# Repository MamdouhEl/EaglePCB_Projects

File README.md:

# EaglePCB_Projects
Here Eagle PCB projects can be found

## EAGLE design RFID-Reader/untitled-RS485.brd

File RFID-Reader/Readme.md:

This PCB was used to mount the "RI-STU-MRD2" RFID Reader Module and connect with Arduino Board and Kinco PLC.

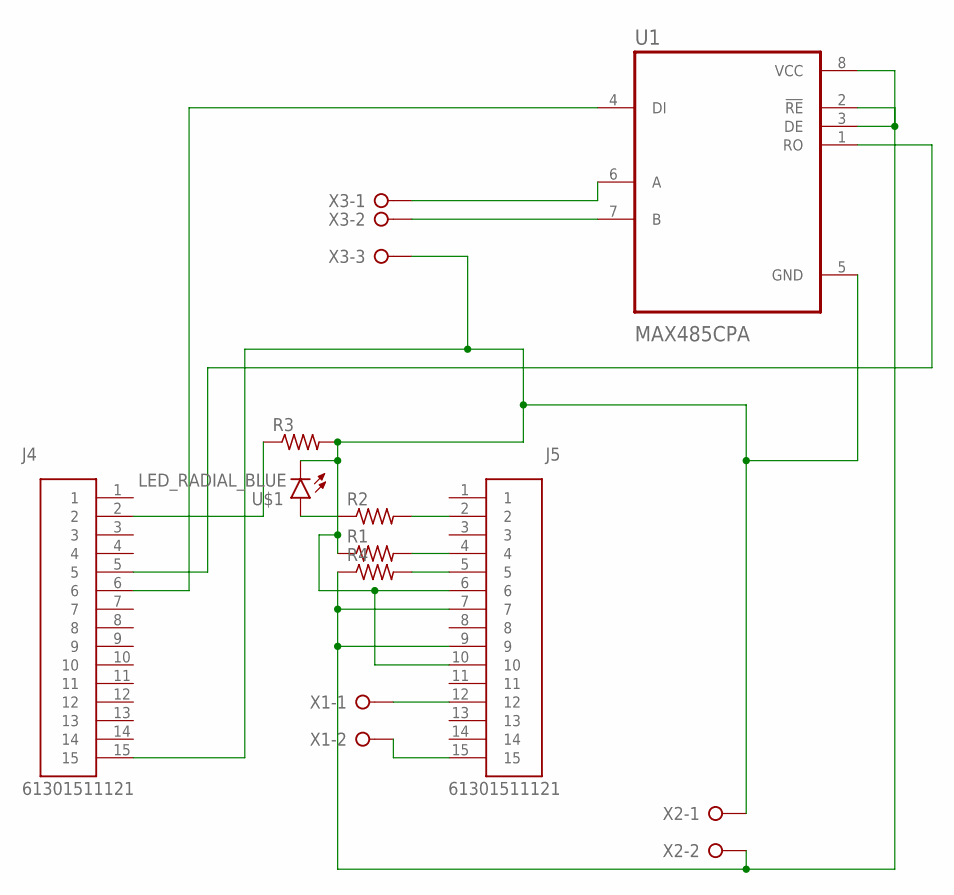
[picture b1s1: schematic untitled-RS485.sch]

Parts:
J4, J5: 61301511121
R1, R2, R3, R4: R-US_0207/7; 0207/7
U1: MAX485CPA; DIP794W47P254L991H457Q8
U$1: LED_RADIAL_BLUE; LEDRD254W60D565H860B_B
X1, X2: W237-02P; W237-132
X3: W237-03P; W237-133

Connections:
unnamed: J4.2, R3.1
unnamed: J5.5, R4.2
unnamed: J4.5, U1.1 (RO)
unnamed: J4.6, U1.4 (DI)
unnamed: J5.2, R2.2
unnamed: R2.1, U$1.1 (A)
unnamed: U1.7 (B), X3.2
unnamed: J5.4, R1.2
unnamed: J4.15, J5.6, J5.10, R1.1, R3.2, U1.5 (GND), U$1.2 (C), X2.1, X3.3
unnamed: U1.6 (A), X3.1
unnamed: J5.7, J5.9, R4.1, U1.2 (!RE), U1.3 (DE), U1.8 (VCC), X2.2
unnamed: J5.12, X1.1
unnamed: J5.15, X1.2

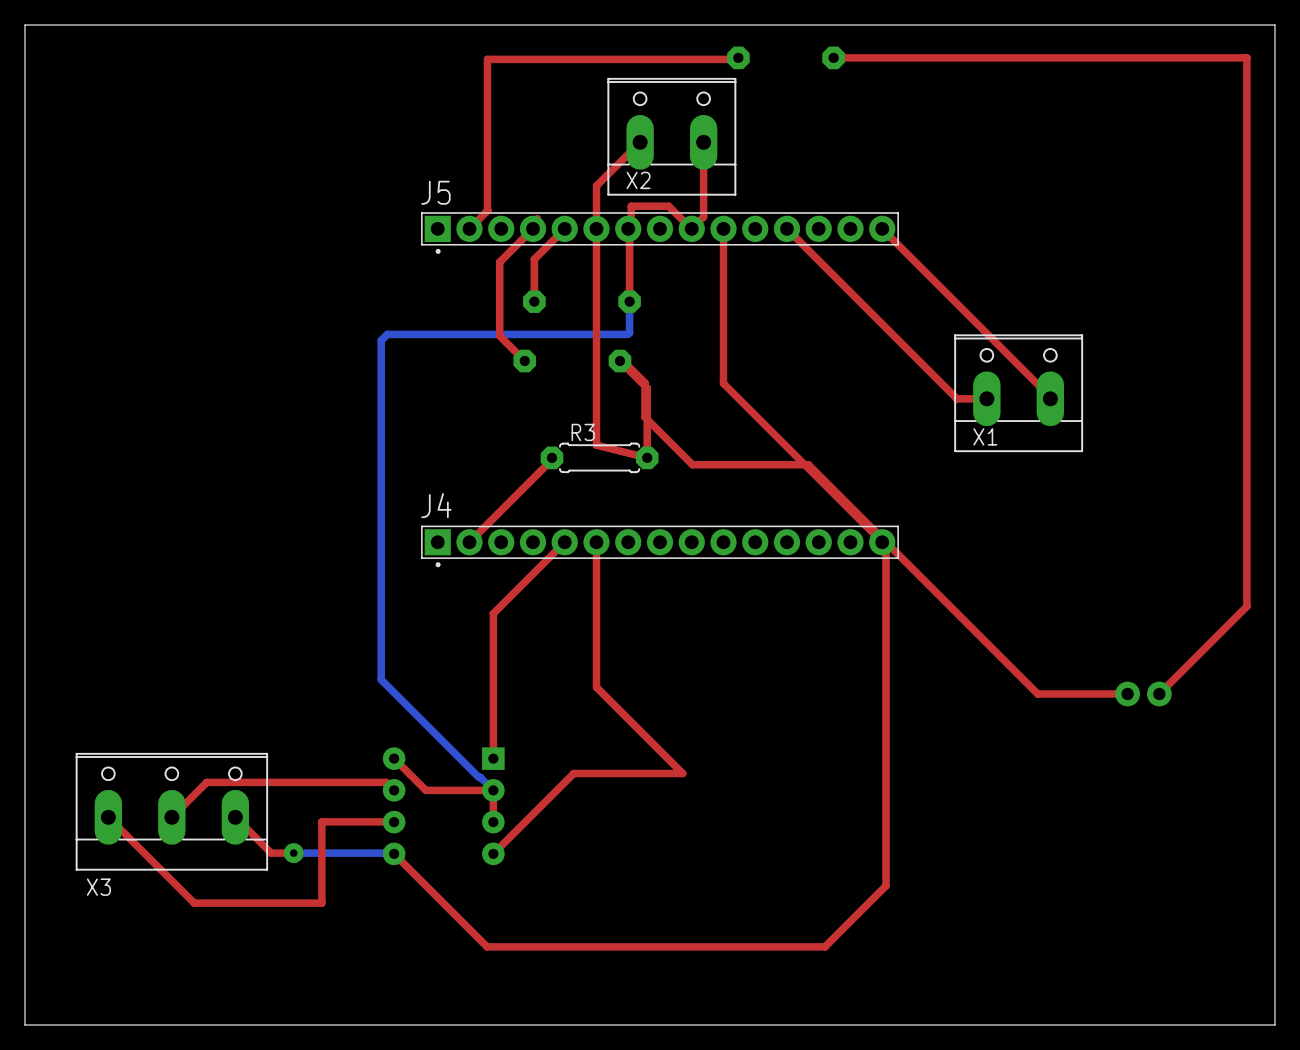
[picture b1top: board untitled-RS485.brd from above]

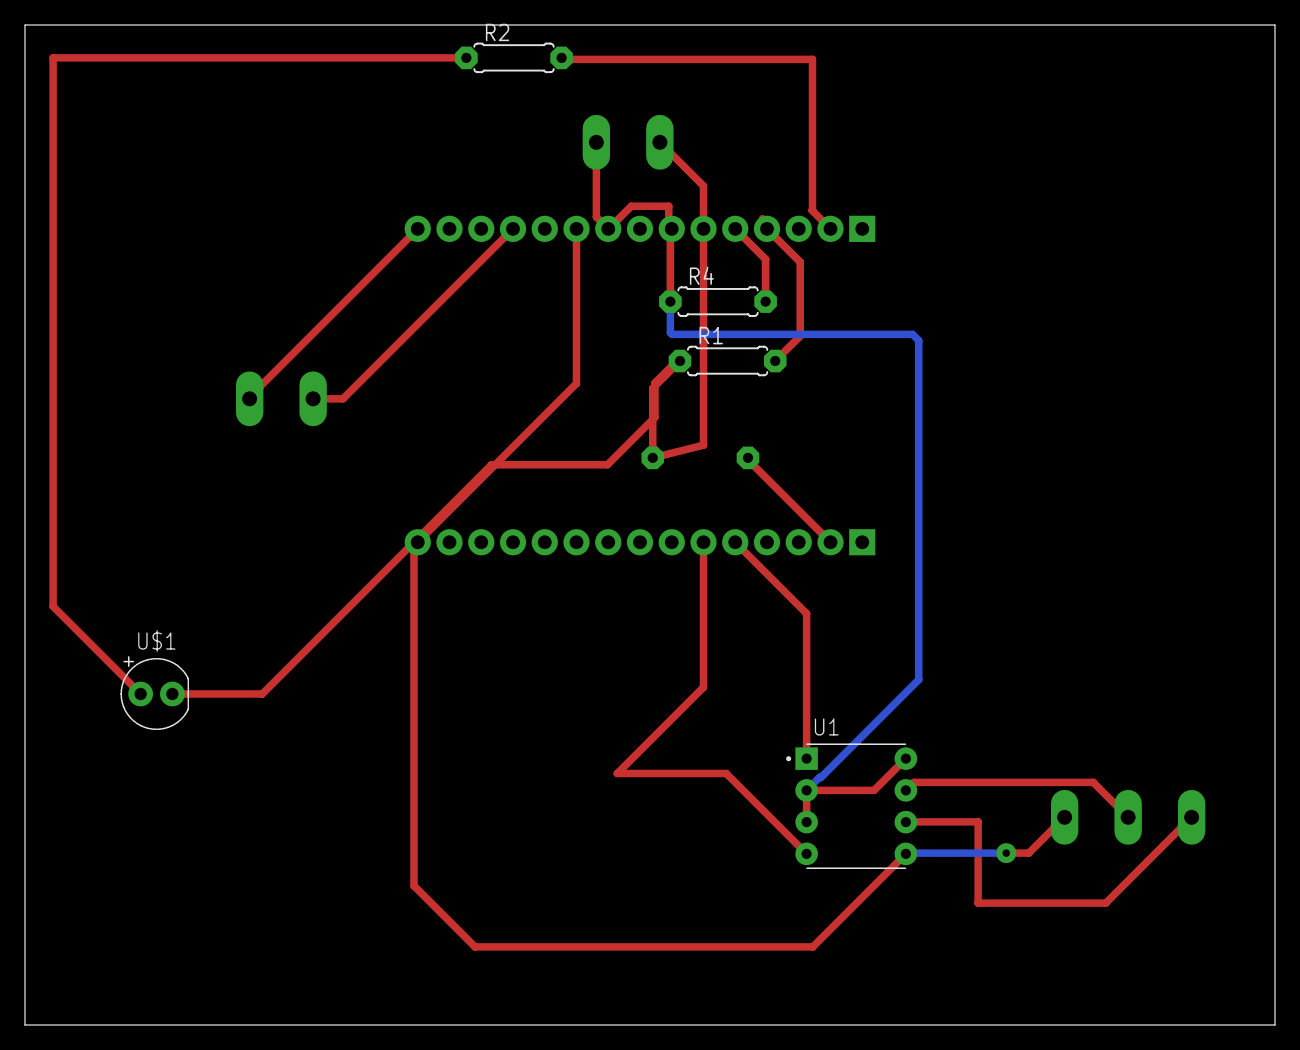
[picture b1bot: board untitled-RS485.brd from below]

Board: 2 copper layers, 100.0 x 80.0 mm, 11 parts (5 on the bottom side), 13 nets.

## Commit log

2023-05-28 Add files via upload
    This PCB board was used to mount the "RI-STU-MRD2" RFID Reader Module with Arduino board and Kinco PLC.
